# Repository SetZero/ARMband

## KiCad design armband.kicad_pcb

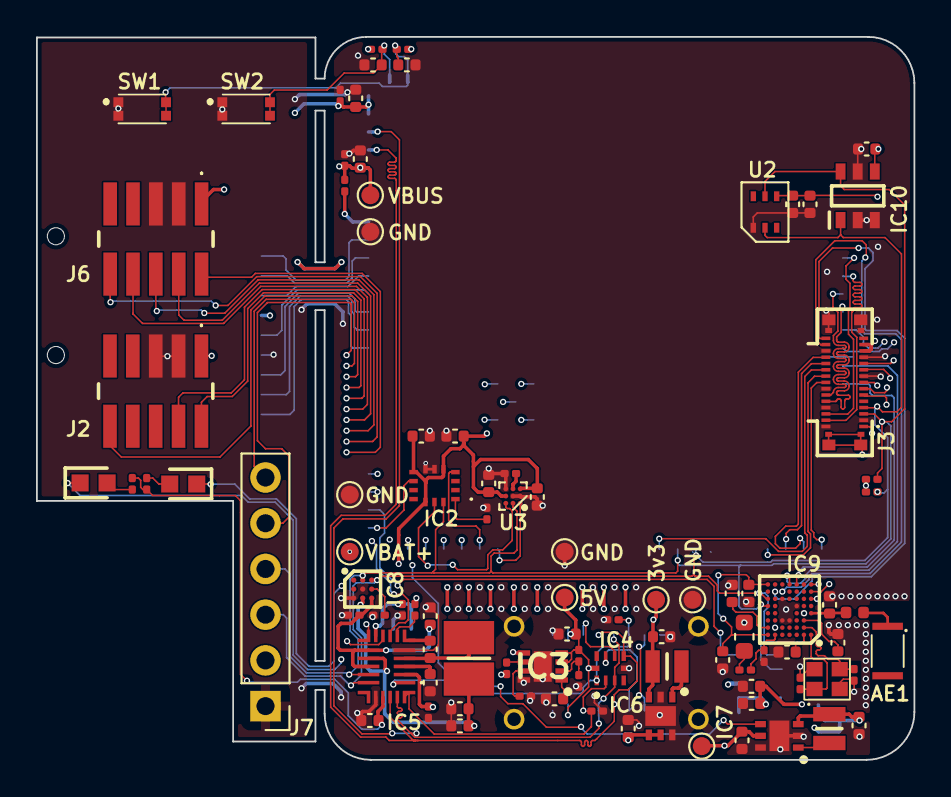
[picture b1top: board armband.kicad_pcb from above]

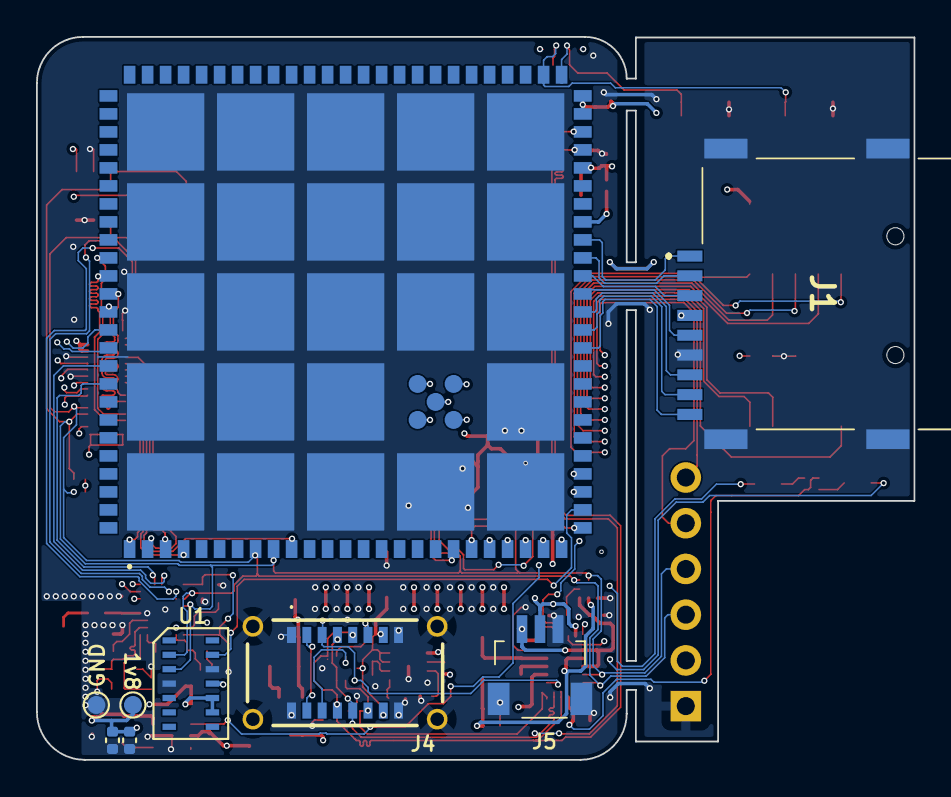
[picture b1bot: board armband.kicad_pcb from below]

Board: 6 copper layers, 48.8 x 40.2 mm, 101 parts (9 on the bottom side), 90 nets.

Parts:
AE1: Antenna_Chip; ST0147-00-011-A
C1, C2, C4, C6, C7, C8, C9, C25, C26, C29, C30, C31, C33, C40, C41: 100n 16V; C_0402_1005Metric
C3, C5, C11, C22, C32: 1u 6.3V; C_0201_0603Metric
C10: 3n3 50V; C_0402_1005Metric
C12: 22n 25V; C_0402_1005Metric
C13, C14, C15, C16, C17, C19, C20, C21, C27, C28: 10u 6.3V; C_0402_1005Metric
C18, C24, C34: 4u7 6.3V; C_0402_1005Metric
C23, C42: 2u2 6.3V; C_0201_0603Metric
C35, C36: 100p; C_0402_1005Metric
C37, C38: 12p 50V; C_0201_0603Metric
C39: 0p8 16V; C_0402_1005Metric
D1, D2: LED_Small; LEDC1608X80N
IC1: QSMP-1570; QSMP1570_better
IC2: BMI323
IC3: TPS259571DSGR; SON50P200X200X80-9N
IC4: TPD6E001RSERG4
IC5: MP2722GRH-0000-Z; MP2722GRH0000Z
IC6: TPS62291DRVR; SON65P200X200X80-7N
IC7: TPS62293DRVR; SON65P200X200X80-7N
IC8: BQ27427YZFR; BGA9C50P3X3_158X162X62
IC9: nRF52832-CIAA-G-R7; BGA50C40P7X8_296X323X40
IC10: TLE493DW2B6A0HTSA1; SOT95P280X110-6N
J1: MEM2075-00-140-01-A; MEM20750014001A
J2, J6: Conn_02x05_Odd_Even; 2002112100010T4LF
J3: AXF5D3012; display_AXF5D3012
J4: UJ20-C-V-SMT-TR-68; UJ20CVSMTTR68
J5: SM03B-SRSS-TB_LF__SN_; SM03BSRSSTBLFSN
J7: Conn_01x06; PinHeader_1x06_P2.54mm_Vertical
L1: 2u2; INDC3225X120N
L2, L3: 2u2; LQM2MPN1R0NG0L
L4: 10u; L_0603_1608Metric
L5: 15n; L_0201_0603Metric
L6: 3n9; L_0402_1005Metric
R1, R2, R3, R4, R6, R13: 10k; R_0201_0603Metric
R5: 0R; R_0201_0603Metric
R7: 1M; R_0201_0603Metric
R8: 100k; R_0201_0603Metric
R9: 383k; R_0201_0603Metric
R10: 1k; R_0201_0603Metric
R11, R12: 5k1 50mW; R_0201_0603Metric
R14: R_Small; R_0201_0603Metric
R15, R16: 92R; R_0201_0603Metric
SW1, SW2: EVP-BB2A9B000; EVPBB2A9B000
TP1, TP2, TP3, TP4, TP5, TP6, TP7, TP8, TP9, TP10, TP11: TestPoint; TestPoint_Pad_D1.0mm
U1: MAX30102
U2: VEML3235
U3: BMM350; bmm350
Y2: Crystal_GND24; CX2016SA

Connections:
+1V8: C7.1, C8.1, C20.1, C24.1, C25.1, C40.1, C41.1, IC2.5 (VDDIO), IC2.8 (VDD), IC2.12 (CSB), IC7.3 (FB), J3.13 (VIO18), J3.14 (VIO18), L3.1, TP5.1, U1.11 (VDD), U3.B3 (VDDIO), U3.C1 (VDD)
+3V3: C3.1, C4.1, C16.1, C26.1, C27.1, C28.1, C29.1, C30.1, IC1.49 (VIN_1), IC1.50 (VIN_2), IC6.3 (FB), IC10.4 (VDD), J1.P4 (VDD), J2.1, J3.8 (TP_VDD), J3.31 (VPH_PWR), J6.1, J7.2, L2.1, R1.1, R2.1, R3.1, R4.1, R8.1, TP4.1, U1.9 (VLED+), U1.10 (VLED+), U2.4 (VDD)
/supply/VIN_FAULT: IC3.6 (~FLT), R8.2
BMI_INT1: IC1.20 (ENET_CK125), IC2.4 (INT1)
BMI_INT2: IC1.26 (ENET_RXD0), IC2.9 (INT2)
BMM350_INT: IC1.19 (ENET_RST), U3.A1 (INT)
BT_ANT: C39.1, IC9.D1 (ANT), L6.2
DEC2: C35.1, IC9.A2 (DEC2)
DEC3: C36.1, IC9.C2 (DEC3)
DEC4: C32.1, IC9.A6 (DEC4), L5.1
GND: C1.2, C2.2, C3.2, C4.2, C5.2, C6.2, C7.2, C8.2, C9.2, C10.2, C11.2, C13.2, C14.2, C15.2, C16.2, C17.2, C18.2, C19.2, C20.2, C21.2, C22.2, C23.2, C24.2, C25.2, C26.2, C27.2, C28.2, C29.2, C30.2, C31.2, C32.2, C33.2, C34.1, C35.2, C36.2, C37.2, C38.2, C39.2, C40.2, C41.2, C42.2, IC1.101 (EP_1), IC2.6 (GNDIO), IC2.7 (GND), IC3.8 (GND_1), IC3.9 (GND_2), IC4.5 (GND), IC5.5 (PGND), IC5.18 (AGND), IC6.2 (MODE), IC6.6 (GND), IC6.7 (EP), IC7.2 (MODE), IC7.6 (GND), IC7.7 (EP), IC8.B2 (VSS_1), IC8.C1 (VSS_2), IC9.C4 (VSS_1), IC9.C5 (VSS_2), IC9.D2 (VSS_PA), IC9.E3 (VSS_3), IC9.F5 (VSS_4), IC10.2 (GND), IC10.3 (GND_2), IC10.5 (GND_3), J1.MP1, J1.MP2, J1.MP3, J1.MP4 (MP), J1.P6 (VSS), J2.3, J2.5, J3.2 (GND), J3.9 (GND), J3.12 (GND), J3.18 (GND), J3.24 (GND), J3.27 (GND), J3.30 (GND), J4.A1 (GND_1), J4.A12 (GND_2), J4.B1 (GND_3), J4.B12 (GND_4), J4.MH1, J4.MH2, J4.MH3, J4.MH4, J5.3 (GND), J5.MP1 (MP), J5.MP2 (MP), J6.3, J6.5, J7.1, R6.2, R9.2, R10.2, R11.2, R12.2, R14.2, SW1.1 (A), SW2.1 (A), TP7.1, TP8.1, TP9.1, TP10.1, TP11.1, U1.4 (PGND), U1.12 (GND), U2.1 (GND), U3.B1 (GND), U3.B2 (ADSEL), U3.C3 (BYPASS), Y2.2, Y2.4
JTAG_NRST: IC1.A1 (JTAG_TRST_B), J6.10
JTAG_TCK: IC1.C3 (JTAG_TCK), J6.4
JTAG_TDI: IC1.C1 (JTAG_TDI), J6.8
JTAG_TDO: IC1.B2 (JTAG_TDO), J6.6
JTAG_TMS: IC1.A3 (JTAG_TMS), J6.2
LCD_RST: IC1.22 (ENET_MDIO), J3.10 (LCD_RST)
LCD_TE: IC1.21 (ENET_INT), J3.11 (LCD_TE)
MAX_INT: IC1.27 (ENET_RXD1), U1.13 (~INT)
MP2722_INT: IC1.28 (ENET_RXD2), IC5.8 (~INT)
NFC_ANT1: IC9.G6 (NFC1/P0.09), J3.16 (NFC_ANT2)
NFC_ANT2: IC9.G5 (NFC2_/P0.10), J3.17 (NFC_ANT1)
NRF_NRST: IC9.H1 (P0.21_/NRESET), J2.10
NRF_SWCLK: IC9.F1 (SWDCLK), J2.4
NRF_SWDIO: IC9.G1 (SWDIO), J2.2
unnamed: AE1.1 (FEED), L6.1
unnamed: D1.2 (A), R15.1
unnamed: D1.1 (K), IC5.9 (PG/_NTC2)
unnamed: D2.2 (A), R16.1
unnamed: D2.1 (K), IC5.11 (STAT/_IB)
unnamed: IC1.43 (USBA_VBUS), R5.2
unnamed: IC2.1 (SDO), R6.1
unnamed: C10.1, IC3.1 (DVDT)
unnamed: IC3.2 (EN/UVLO), R7.2, R9.1
unnamed: IC3.7 (ILM), R10.1
unnamed: C9.1, IC3.3 (IN_1), IC3.4 (IN_2), IC4.10 (VCC), J4.A4 (VBUS_1), J4.A9 (VBUS_2), J4.B4 (VBUS_3), J4.B9 (VBUS_4), R7.1, TP2.1
unnamed: IC4.1 (IO1), IC5.1 (CC1), J4.A5 (CC1), R11.1
unnamed: IC4.2 (IO2), IC5.22 (CC2), J4.B5 (CC2), R12.1
unnamed: IC4.7 (IO5), J4.A8 (SBU1)
unnamed: IC4.8 (IO6), J4.B8 (SBU2)
unnamed: C12.2, IC5.6 (BST)
unnamed: C21.1, IC5.3 (PMID)
unnamed: C12.1, IC5.4 (SW), L1.1
unnamed: C18.1, IC5.19 (VCC), R15.2, R16.2
unnamed: IC5.7 (VRNTC), R13.1
unnamed: IC6.1 (SW), L2.2
unnamed: IC7.1 (SW), L3.2
unnamed: C23.1, IC8.B3 (VDD)
unnamed: IC9.B6 (DCC), L4.2
unnamed: C31.1, IC9.B7 (DEC1)
unnamed: C33.1, C34.2, IC9.A7 (VDD_1), IC9.H7 (VDD_2)
unnamed: C37.1, IC9.B2 (XC1), Y2.3
unnamed: C38.1, IC9.A1 (XC2), Y2.1
unnamed: J3.5 (NC), J3.15 (NC)
unnamed: L4.1, L5.2
unnamed: C42.1, U3.C2 (CRST)
QSMP_BOOT: C1.1, IC1.52 (BOOT_MODE), R1.2, SW1.2 (B)
QSMP_BUCK_1V8_EN: IC1.29 (ENET_RXD3), IC7.4 (EN)
QSMP_DCX: IC1.10 (INTB), J3.21 (SPI_DCX)
QSMP_DSI_CLKN: IC1.88 (DSI_CKN_LVDS0_CLKN), J3.26 (MIPI_CLKN)
QSMP_DSI_CLKP: IC1.87 (DSI_CKP_LVDS0_CLKP), J3.25 (MIPI_CLKP)
QSMP_DSI_D0N: IC1.86 (DSI_DN0_LVDS0_TX0N), J3.29 (MIPI_DON)
QSMP_DSI_D0P: IC1.85 (DSI_DP0_LVDS0_TX0P), J3.28 (MIPI_DOP)
QSMP_LCD_EN: IC1.25 (ENET_RX_CTL), J3.1 (VCI_EN)
QSMP_MISO: IC1.2 (SPIA_MISO), J3.19 (SPI_SDO)
QSMP_MOSI: IC1.3 (SPIA_MOSI), J3.20 (SPI_SDI)
QSMP_NRST: C2.1, IC1.51 (NRST_PWREN), R2.2, SW2.2 (B)
QSMP_RXD_DEBUG: IC1.89 (UARTA_RXD), J7.5
QSMP_RXD_NRF: IC1.91 (UARTB_RXD), IC9.H4 (P0.15/TRACEDATA[2])
QSMP_SCK: IC1.4 (SPIA_SCK), J3.22 (SPI_CLK)
QSMP_SCL: IC1.8 (I2CB_SCL), IC2.13 (SCX), IC5.16 (SCL), IC8.A3 (SCL), IC9.F7 (P0.06), IC10.1 (SCL_/INT), J3.4 (TP_12C_SCL), J7.3, R3.2, U1.2 (SCL), U2.2 (SDA), U3.A3 (SCK)
QSMP_SDA: IC1.9 (I2CB_SDA), IC2.14 (SDX), IC5.15 (SDA), IC8.A2 (SDA), IC9.E7 (P0.05/_AIN3), IC10.6 (SDA), J3.3 (TP_12C_SDA), J7.4, R4.2, U1.3 (SDA), U2.5 (SCL), U3.A2 (SDA)
QSMP_SS: IC1.1 (SPIA_NSS), J3.23 (SPI_CS)
QSMP_TXD_DEBUG: IC1.90 (UARTA_TXD), J7.6
QSMP_TXD_NRF: IC1.92 (UARTB_TXD), IC9.H3 (P0.16_/TRACEDATA[1])
QSMP_USB_DN: IC1.47 (USBB_DN), IC4.6 (IO4), IC5.20 (D-), J4.A7 (DN1), J4.B7 (DN2)
QSMP_USB_DP: IC1.48 (USBB_DP), IC4.3 (IO3), IC5.21 (D+), J4.A6 (DP1), J4.B6 (DP2)
QSMP_VBUS: C5.1, C6.1, C11.1, IC1.46 (USBB_VBUS), IC3.5 (OUT), IC5.2 (IN), R5.1, TP1.1
SD_CD: IC1.36 (SD_CD), J1.P9 (CD)
SD_CLK: IC1.39 (SD_CLK), J1.P5 (CLK)
SD_CMD: IC1.40 (SD_CMD), J1.P3 (CMD)
SD_D0: IC1.38 (SD_D0), J1.P7 (DAT0)
SD_D1: IC1.37 (SD_D1), J1.P8 (DAT1)
SD_D2: IC1.42 (SD_D2), J1.P1 (DAT2)
SD_D3: IC1.41 (SD_D3), J1.P2 (CD/DAT3)
TH_BAT: IC5.10 (NTC1), J5.2 (TH), R13.2, R14.1
TP_INT: IC1.23 (ENET_MDC), J3.7 (TP_INT)
TP_RST: IC1.24 (ENET_RXC), J3.6 (TP_RST)
VBAT+: C17.1, C22.1, IC5.12 (BATTSNS), IC5.14 (BATT), IC8.C3 (BAT), J5.1 (VCC), TP6.1
VSYS: C13.1, C14.1, C15.1, C19.1, IC5.13 (SYS), IC6.4 (EN), IC6.5 (VIN), IC7.5 (VIN), IC8.C2 (SRX), L1.2, TP3.1

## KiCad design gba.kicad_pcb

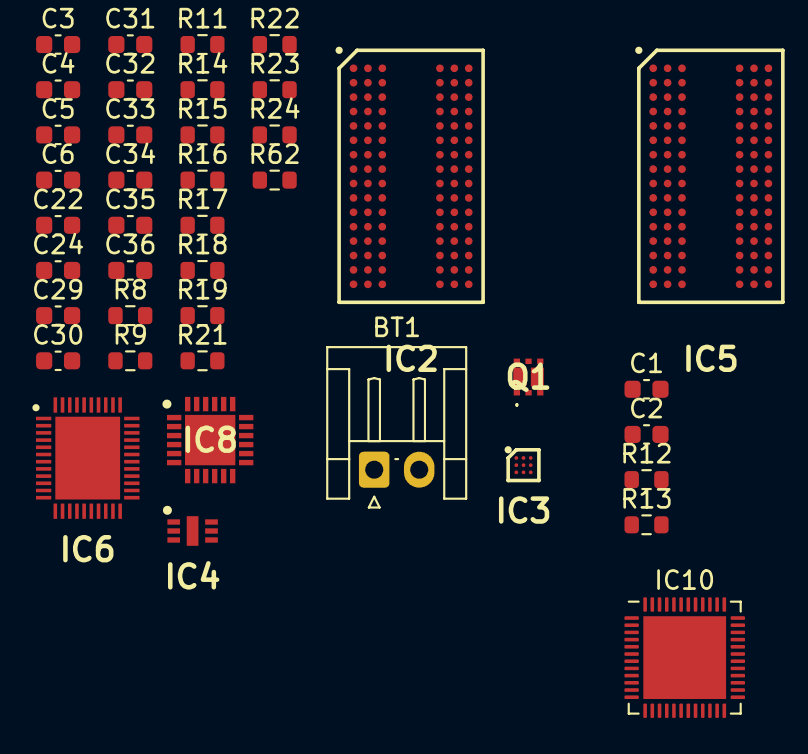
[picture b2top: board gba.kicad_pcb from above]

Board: 2 copper layers, 41 parts (0 on the bottom side), 30 nets, no tracks yet.

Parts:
BT1: Battery_Cell; JST_EH_S2B-EH_1x02_P2.50mm_Horizontal
C1, C2: 10n; C_0603_1608Metric
C3, C4, C5, C6, C22, C24, C36: 10u; C_0603_1608Metric
C29, C33, C34, C35: 1u; C_0603_1608Metric
C30: 220n; C_0603_1608Metric
C31, C32: 4u7; C_0603_1608Metric
IC2, IC5: MT41K256M16TW-107_P; BGA96C80P9X16_800X1400X120
IC3: STC3117IJT; BGA9C40P3X3_146X156X66
IC4: MCP73830T-2AAI_MYY; SON50P200X200X80-7N-D
IC6: STPMIC1BPQR; QFN40P500X600X80-45N-D
IC8: STUSB1600AQTR; QFN50P400X400X100-25N
IC10: nRF52832-QFAA-R7; QFN-48-1EP_6x6mm_P0.4mm_EP4.6x4.6mm
Q1: PMDPB70XP_115; PMDPB70XP115
R8, R9, R14, R15, R17, R21: 1k; R_0603_1608Metric
R11, R12, R13, R16, R18, R19, R22, R23, R24: 10k; R_0603_1608Metric
R62: 0R; R_0603_1608Metric

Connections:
BSTOUT: IC6.34 (BOUT), IC6.37 (SWIN)
BUCK2_1V35: C24.2, IC2.A1 (VDDQ_1), IC2.A8 (VDDQ_2), IC2.B2 (VDD_1), IC2.C1 (VDDQ_3), IC2.C9 (VDDQ_4), IC2.D2 (VDDQ_5), IC2.D9 (VDD_2), IC2.E9 (VDDQ_6), IC2.F1 (VDDQ_7), IC2.G7 (VDD_3), IC2.H2 (VDDQ_8), IC2.H9 (VDDQ_9), IC2.K2 (VDD_4), IC2.K8 (VDD_5), IC2.N1 (VDD_6), IC2.N9 (VDD_7), IC2.R1 (VDD_8), IC2.R9 (VDD_9), IC6.9 (VOUT2), IC6.13 (LDO3IN)
BUCK3_3V3: C35.2, IC6.31 (VOUT3), IC8.22 (VSYS)
BUCK4_1V8: IC6.27 (VOUT4), IC6.42 (VIO), IC10.13 (VDD_1), IC10.36 (VDD_2), IC10.48 (VDD_3), R11.1, R12.1, R13.1, R18.2, R19.2, R22.2, R23.2, R24.2
GND: C1.2, C2.2, C3.1, C4.1, C5.1, C6.1, C22.1, C24.1, C29.1, C30.1, C31.1, C32.1, C33.1, C34.1, C35.1, C36.2, IC2.A9 (VSS_1), IC2.B1 (VSSQ_1), IC2.B3 (VSS_2), IC2.B9 (VSSQ_2), IC2.D1 (VSSQ_3), IC2.D8 (VSSQ_4), IC2.E1 (VSS_3), IC2.E2 (VSSQ_5), IC2.E8 (VSSQ_6), IC2.F9 (VSSQ_7), IC2.G1 (VSSQ_8), IC2.G8 (VSS_4), IC2.G9 (VSSQ_9), IC2.J2 (VSS_5), IC2.J8 (VSS_6), IC2.M1 (VSS_7), IC2.M9 (VSS_8), IC2.P1 (VSS_9), IC2.P9 (VSS_10), IC2.T1 (VSS_11), IC2.T9 (VSS_12), IC3.A3 (GND), IC4.1 (VSS), IC4.7 (EP), IC6.6 (PGND1), IC6.10 (PGND2), IC6.15 (GNDLDO), IC6.26 (PGND4), IC6.30 (PGND3), IC6.41 (AGND), IC6.45 (EPGND), IC8.3 (VCONN), IC8.10 (GND), IC8.13 (ADDR0), IC8.25 (THERMAL_PAD), IC10.31 (VSS_1), IC10.45 (VSS_2), IC10.49 (THERMAL_PAD), R14.2, R21.2
unnamed: BT1.2 (-), IC3.B3 (CS), R9.2
unnamed: IC3.B1 (BATD), R9.1
unnamed: C30.2, IC3.C1 (VIN), R8.2
unnamed: IC4.6 (PROG), R14.1
unnamed: IC4.2 (STAT), R15.2
unnamed: IC8.19 (VBUS_EN_SNK), R17.2
unnamed: IC8.24 (VDD), Q1.1 (S1), Q1.4 (S2), R16.1
unnamed: C33.2, IC8.21 (VREG_1V2)
unnamed: C34.2, IC8.23 (VREG_2V7)
unnamed: Q1.2 (G1), Q1.5 (G2), R16.2, R17.1
PROT_ALM: IC3.C3 (ALM), R11.2
SCL: IC3.B2 (SCL), IC8.7 (SCL), R12.2
SDA: IC3.A2 (SDA), IC8.8 (SDA), R13.2
USB_ALERT#: IC8.9 (ALERT#), R23.1
USB_ATTACH: IC8.12 (ATTACH), R19.1
USB_A_B_SIDE: IC8.17 (A_B_SIDE), R24.1
USB_CC1: IC8.1 (CC1DB), IC8.2 (CC1)
USB_CC2: IC8.4 (CC2), IC8.5 (CC2DB)
USB_DEBUG1: IC8.14 (DEBUG1), R18.1
USB_RESET: IC8.6 (RESET), R21.1
USB_VBUS_VALID: IC8.11 (VBUS_VALID), R22.1
VBAT+: BT1.1 (+), C3.2, C4.2, C5.2, C6.2, C22.2, C29.2, C32.2, IC3.C2 (VCC), IC4.3 (VBAT), IC6.8 (BUCK1IN), IC6.12 (BUCK2IN), IC6.19 (LDO25IN), IC6.22 (LDO16IN), IC6.24 (BUCK4IN), IC6.28 (BUCK3IN), IC6.36 (VIN), R8.1
VIN: C36.1, IC8.18 (VUS_SENSE), Q1.6 (D1_1), Q1.7 (D1_2), R62.1
VIN_BAT_CHRG: C31.2, IC4.4 (VDD), Q1.3 (D2_1), Q1.8 (D2_2), R62.2
VREFCA: IC2.H1 (VREFDQ), IC2.M8 (VREFCA), IC6.16 (VREFDDR)

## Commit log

2023-02-11 Initial Files
2023-02-12 Change Symbols / Footprintst to local library
2023-02-13 added two mp1 footprint versions
2023-02-13 deleted wrong footprints from library. added symbol and footprint for mp1.
2023-02-16 Modified STM32 Symbol: - moved supply in seperate unit
2023-02-19 Connected power rails to mp1
2023-02-19 added VREV_DDR
2023-02-19 Added Symbols
    - MCP73830T
    - STPMIC1BPQR
    - MT41K256M16TW
    - MCP73830
2023-02-19 Added Footprints
    - MCP73830T
    - STPMIC1BPQR
    - MT41K256M16TW
    - MCP73830
2023-02-19 Updated Symbols + Added Supply connections
2023-02-19 Added eMMC (S40FC004C1B2C00000)
2023-02-20 Update eMMC Chip
2023-02-20 Add comment regarding RAM voltage via software
2023-02-22 Added gas gauge and Li-Ion charging
2023-02-22 Added Connectors
2023-02-23 Added STUSB1600A chip
2023-02-24 added some part footprints
2023-02-26 Add Labels for DDR & DDR Power
2023-02-27 Add DDR routing to STM32MP1
2023-02-27 Add documentation to DDR routing
2023-02-27 Add Uart to MPU
2023-02-28 Add SDcard Adapter
2023-03-01 Added Q1 totem-pole circuit for STUSB. Moved components for better visibility.
2023-03-01 3v3 to 1V8 rework
2023-03-01 cleanup schematic
2023-03-01 Add level shifter for uSD
2023-03-02 Add SDCard connection to mpu
2023-03-02 Add SDCard Label
2023-03-05 Added nRF Bluetooth Chip
2023-03-07 added footprint for nRF, changed symbol background color, checked connections
2023-03-08 added supply to nRF
2023-03-08 added decoupling capacitors to mp1
2023-03-09 fixed MP1_VDDA_1V8_REG connection
2023-03-19 changed mp1 symbol and moved BYPASS_REG1V8 signal to supply
2023-03-19 added I2C4 connection to I2C bus and MP1
2023-03-19 Added I2C interface to pmic and stp
2023-04-01 added Murata 1YN wifi + blt chip
2023-04-01 added Murata 1YN.kicad_mod
2023-04-01 Added power to murata 1YN
2023-04-20 Added UART to 1YN
2023-04-21 Added STM32MP157AAB_LFBGA354.kicad_mod
2023-05-19 1YN BT/WLAN connections
2023-05-19 Add CubeMX File for STM32MP157
2023-05-19 Add missing Footprints for SDCard
2023-05-19 part cleanup and name change
2023-08-14 first power management layout iteration, added footprints and values to parts that had none
2023-08-14 added first layout iteration for RAM
2023-08-15 Add missing footprints to components
2023-08-16 added antenna footprints + solder jumper
    removed gba.kicad_pro
2023-08-16 added usb connector and usb pin header footprint
2023-08-16 added missing resistors, removed "LibraryLoaderHatesMe" Symbol library
2023-08-16 Update local symbols for DDR Pins to global
2023-08-16 reworked RAM
2023-08-16 reworked RAM layout
2023-08-20 Fix RAM Labels
2023-08-21 added flash
2023-08-21 removed unneccessary parts + first ram layout iteration
2023-08-21 ddr3 routing progress
2023-08-22 progressed ram layout (connected communication pins)
2023-08-23 added dummy resistors for ddr3 layout connections and progressed layout
2023-09-23 clock lines
2023-09-23 clock meander madness
2023-09-23 Add Net Classes + CLK length matching
2023-09-23 Add vias and routes for addr lines
2023-09-23 connected address pins of ddr3
2023-09-26 first length matching iteration
2023-09-26 Change DDR clk length from 40 to 37mm
2023-09-28 Add wiring for Data lines + remove ground layer in favor for signal layer
2023-09-30 cleaned traces, reworked and lengthmatched datalines
2023-09-30 Check and fix length matching
2023-10-01 Fix some DRC warnings
2023-10-01 loeschanfall + new start
2023-10-02 reworked currently set traces, constrained length of address traces between 18 and 26mm
2023-10-02 Add termination resistor conenctions + via for DQ
2023-10-14 routed datalines - gl lengthmatching that!
2023-11-24 preperation for lengthmatching (probably 24.5mm +- 0.635)
2023-11-25 progressed length matching
2023-11-25 lengthmatched ddr traces to 24.5mm +-0.625mm
2023-12-11 lengthmatching finalized
    clk_p, clk_n also matched to 24.5mm
2023-12-15 created first power plane sub-section
2023-12-15 added power planes
2023-12-18 added QSMP1570 symbol and footprint to project. Modified Symbol. Cleaning of schematic.
2023-12-19 added boot buttons and voltage rail labels
2023-12-19 added selection of charging ICs as text
2023-12-20 added mezzanine connector for display
2023-12-25 removed old symbols
2023-12-25 Removed components which are not needed anymore
2023-12-25 added debug breakout components (SD, Header for I2C + JTAG)
2023-12-27 added symbols and footprints for peripherals
2023-12-27 Update AXF5D3012 symbol
2023-12-27 added hierachical sheets
2023-12-27 Update Pull-Ups for I2C/Boot/NRST
2023-12-27 progressed charging and gas gauge schematic
2023-12-28 added buck
2023-12-29 added new bucks
2023-12-29 buck circuits
2023-12-29 Add Inductor LQM2MPN2R2MG0L
2023-12-30 added usb connector
2023-12-31 added usb protection
2024-01-01 Update capacitor values
2024-01-01 finished usb connection ciruits
2024-01-01 switched to other charge + protection IC
2024-01-01 Update resistors + LED values
2024-01-02 Add MNR for LED
2024-01-02 fixed display connector
2024-01-02 added TVS diodes and cleaned up supply.kicad_sch
2024-01-02 Add i2c device list
2024-01-04 added decoupling capacitors to sensors
2024-01-04 added signal connections to QSMP
2024-01-05 cleaned up supply labels
2024-01-05 added buttons (with symbol that is not trash)
2024-01-05 added SBU pins to TVS diodes, changed button pullup resistors (QSMP)
2024-01-05 added ambient light_sensor.kicad_sch
2024-01-08 cleaned up symbol fields table and removed unused or duplicate fields.
2024-01-08 switched to I2CB (so both M4 and A7 access), added 1v8 enable gpio and removed connection to vin
2024-01-13 added rotary_encoder.kicad_sch and magnetic sensor for it
2024-01-13 added magnetc sensor address to i2c address table
2024-01-13 Add battery connector footprint
2024-01-13 Update battery connector in schematic
2024-01-13 Add nRF base layout
2024-01-13 added XTAL to nrf chip
2024-01-13 updated BLE + NFC.kicad_sch
    - added antenna footprint
    - added impedance matching
    - added inductors on DCC pin
    - changed various symbol values to match conventions (e.g. 0.9uH -> 0u9)
2024-01-13 updated BLE + NFC.kicad_sch
    - added pins for I2C slave communication
    - added connections to I2C pins and SWD/JTAG interface
2024-01-14 Update JTAG
    Add Footprint for JTAG connector
    Add NRF connections
2024-01-14 updated schematic
    - renamed JTAG (QSMP) and SWD (NRF) labels
    - added footprint to misc. connector in debug.kicad_sch
2024-01-17 added bmm350.kicad_mod and changed 9dof.kicad_sch
    + added symbol and footprint for magnetometer BMM350
    + changed supply of BMI (6dof) to 1v8
2024-01-17 Update 3d models
2024-01-21 changed display footprint
    - added new display_AXF5D3012.kicad_mod (from old AXF5D3012.kicad_mod)
    - updated display symbol to use new footprint
2024-01-21 updated display_AXF5D3012.kicad_mod footprint
    - added outlines
2024-01-21 first layout iteration
2024-02-10 progressed layout, adjusted some courtyard sized to be smaller
2024-02-11 progressed layout
2024-02-11 there was an attempt to length match DSI
2024-02-11 Update length matching
2024-02-12 Add Heartbeat sensor to PCB
2024-02-15 Add debug location
2024-02-16 progressed layout and made changes in bmi323 (set unconnected pins to NC) + changed debug connections in preparation to make bridges to debug part + changed VSYS, VUSB, VBAT+ and other connected powe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
2024-02-16 added edge.cuts
2024-02-16 Reduce DRC findings
2024-02-16 Add debug connections
2024-02-16 Improve some connections
2024-02-17 fixed drc errors
2024-02-17 Update USB length matching
2024-02-18 added QSMP1570_better.kicad_mod and part designators, moved production files into own folder
2024-02-18 Fix unconnected nets
2024-02-18 Add gnd connection for OLED connector
2024-02-18 rounded corners
2024-02-19 fixed unneccessary traces
2024-02-22 added test points
2024-02-22 Added LED
2024-02-23 fixed silkscreen errors
2024-02-23 added logos
2024-02-26 added jlcpcb conform production files
2024-03-01 added missing MFN numbers
2024-03-09 Update to KiCad 8 + Add/Fix voltage selector for nRF
